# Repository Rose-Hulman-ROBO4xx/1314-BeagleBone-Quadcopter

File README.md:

Snoopy Copter
==========================
The quadcopter project got a rename recently. Named for the popular Peanuts character Snoopy, who always dreamed of flight, our flying Beaglebone will hopefully aid Snoopy in his quest to defeat the Red Baron!

Create an inexpensive open-source project for a BeagleBone cape quadcopter. As of the beginning of April, 2014, we have flight! Some videos of the initial flight testing are located [here](https://www.dropbox.com/sh/0pfk43b3zq14rjh/xk6Kl6lccb#/). Since then, the quadcopter has gotten easier to fly and more stable.

## Pictures ##

421 grams!

## License ##
All software and hardware designs (frame, circuit board, etc.) here are under Creative Commons Non-Commercial Share-Alike V3.0 License, located [here](http://creativecommons.org/licenses/by-nc-sa/3.0/us/legalcode).

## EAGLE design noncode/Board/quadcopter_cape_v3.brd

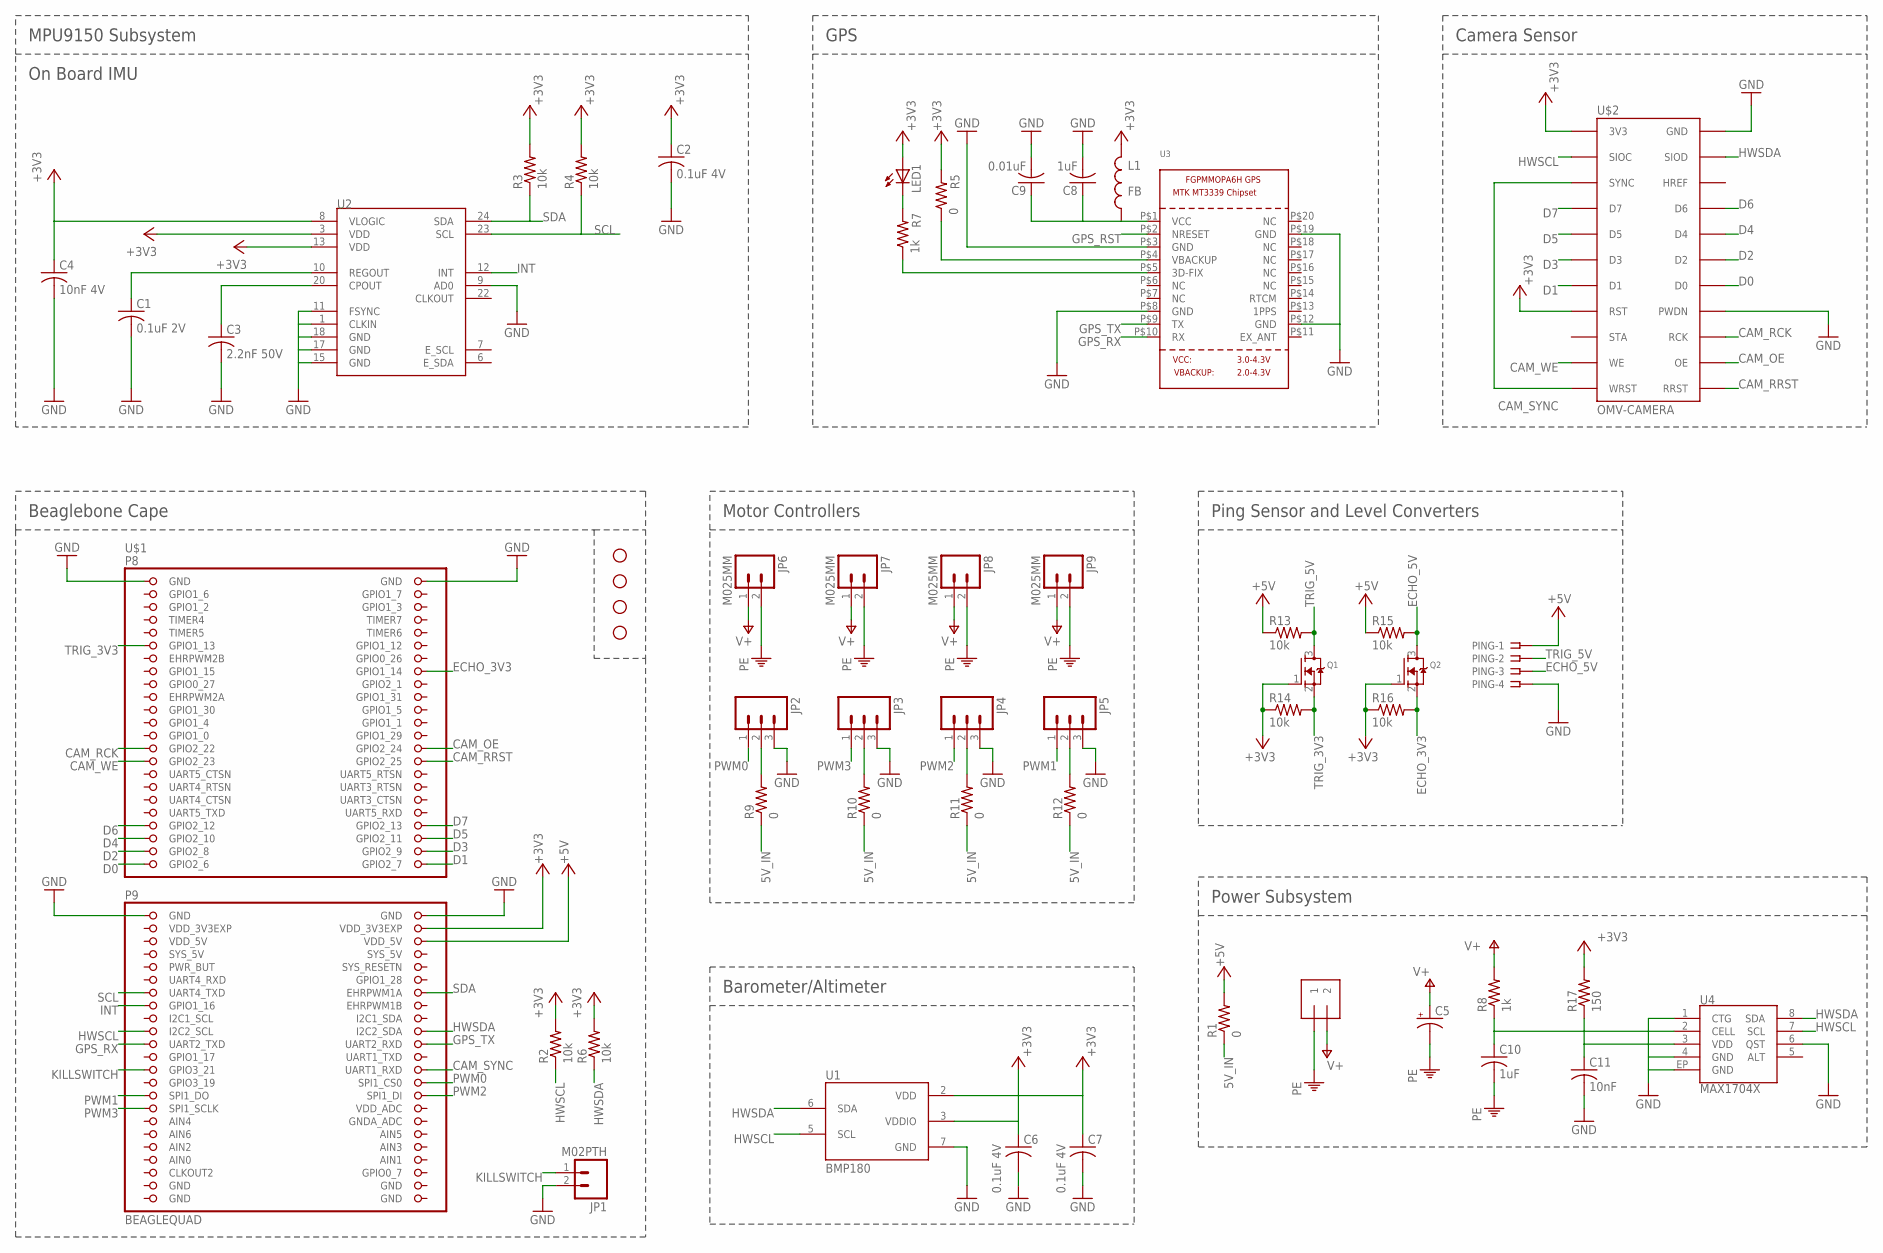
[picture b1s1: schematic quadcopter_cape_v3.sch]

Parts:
C1: 0.1uF 2V; C0805
C2, C6, C7: 0.1uF 4V; C0805
C3: 2.2nF 50V; C0805
C4: 10nF 4V; C0805
C5: 10UF-25V-20%(PTH); CPOL-RADIAL-10UF-25V
C8, C10: 1uF; C0805
C9: 0.01uF; C0805
C11: 10nF; C0805
JP1: M02PTH; 1X02
JP2, JP3, JP4, JP5: M03PTH; 1X03
JP6, JP7, JP8, JP9: M025MM; SCREWTERMINAL-5MM-2
L1: FB; 0805
LED1: LEDCHIP-LED0805; CHIP-LED0805
PING: SSW-104-02-S-S-RA
Q1, Q2: MOSFET-NREFLOW; SOT23
R1, R5, R9, R10, R11, R12: 0; M0805
R2, R3, R4, R6, R13, R14, R15, R16: 10k; M0805
R7, R8: 1k; M0805
R17: 150; M0805
STANDOFF1, STANDOFF2, STANDOFF3, STANDOFF4: STAND-OFF
U1: BMP180
U2: MPU-9150QFN-24-NP; QFN-24-NP
U3: GPS_FGPMMOPA6H; FGPMMOPA6H
U4: MAX1704X; TDFN-8
U$1: BEAGLEQUAD; BEAGLEQUAD_SHIELD
U$2: OMV-CAMERA
U$3: 1X2-12AWG

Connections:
5V_IN: R1.1, R9.1, R10.1, R11.1, R12.1
+3V3: C2.1, C4.1, C6.1, C7.1, L1.2, LED1.A, Q1.1 (G), Q2.1 (G), R2.2, R3.2, R4.2, R5.2, R6.2, R14.1, R16.1, R17.2, U1.2 (VDD), U1.3 (VDDIO), U2.3 (VDD), U2.8 (VLOGIC), U2.13 (VDD), U$1.50 (VDD_3V3EXP), U$2.3V3, U$2.RST
+5V: PING.1, R1.2, R13.1, R15.1, U$1.52 (VDD_5V)
AIN0: U$1.85 (AIN0)
CAM_OE: U$1.28 (GPIO2_24), U$2.OE
CAM_RCK: U$1.27 (GPIO2_22), U$2.RCK
CAM_RRST: U$1.30 (GPIO2_25), U$2.RRST
CAM_SYNC: U$1.72 (UART1_RXD), U$2.SYNC, U$2.WRST
CAM_WE: U$1.29 (GPIO2_23), U$2.WE
D0: U$1.45 (GPIO2_6), U$2.D0
D1: U$1.46 (GPIO2_7), U$2.D1
D2: U$1.43 (GPIO2_8), U$2.D2
D3: U$1.44 (GPIO2_9), U$2.D3
D4: U$1.41 (GPIO2_10), U$2.D4
D5: U$1.42 (GPIO2_11), U$2.D5
D6: U$1.39 (GPIO2_12), U$2.D6
D7: U$1.40 (GPIO2_13), U$2.D7
ECHO_3V3: Q2.2 (S), R16.2, U$1.16 (GPIO1_14)
ECHO_5V: PING.3, Q2.3 (D), R15.2
GND: C1.2, C2.2, C3.2, C4.2, C6.2, C7.2, C8.2, C9.2, C11.2, JP1.2, JP2.3, JP3.3, JP4.3, JP5.3, PING.4, U1.7 (GND), U2.1 (CLKIN), U2.9 (AD0), U2.11 (FSYNC), U2.15 (GND), U2.17 (GND), U2.18 (GND), U3.P$3 (GND), U3.P$8 (GND), U3.P$12 (GND), U3.P$19 (GND), U4.1 (CTG), U4.4 (GND), U4.6 (QST), U4.EP (GND), U$1.1 (GND), U$1.2 (GND), U$1.47 (GND), U$1.48 (GND), U$1.89 (GND), U$1.90 (GND), U$1.91 (GND), U$1.92 (GND), U$2.GND, U$2.PWDN
GPS_RST: U3.P$2 (NRESET)
GPS_RX: U3.P$10 (RX), U$1.67 (UART2_TXD)
GPS_TX: U3.P$9 (TX), U$1.68 (UART2_RXD)
HWSCL: R2.1, U1.5 (SCL), U4.7 (SCL), U$1.65 (I2C2_SCL), U$2.SIOC
HWSDA: R6.1, U1.6 (SDA), U4.8 (SDA), U$1.66 (I2C2_SDA), U$2.SIOD
INT: U2.12 (INT), U$1.61 (GPIO1_16)
KILLSWITCH: JP1.1, U$1.71 (GPIO3_21)
unnamed: C10.1, R8.1, U4.2 (CELL)
unnamed: C1.1, U2.10 (REGOUT)
unnamed: R5.1, U3.P$4 (VBACKUP)
unnamed: C3.1, U2.20 (CPOUT)
unnamed: R7.1, U3.P$5 (3D-FIX)
unnamed: LED1.C, R7.2
unnamed: C8.1, C9.1, L1.1, U3.P$1 (VCC)
unnamed: JP2.2, R9.2
unnamed: JP3.2, R10.2
unnamed: JP4.2, R11.2
unnamed: JP5.2, R12.2
unnamed: C11.1, R17.1, U4.3 (VDD)
PE: C5.2 (-), C10.2, JP6.2, JP7.2, JP8.2, JP9.2, U$3.P$1 (1)
PWM0: JP2.1, U$1.74 (SPI1_CS0)
PWM1: JP5.1, U$1.75 (SPI1_DO)
PWM2: JP4.1, U$1.76 (SPI1_DI)
PWM3: JP3.1, U$1.77 (SPI1_SCLK)
SCL: R4.1, U2.23 (SCL), U$1.59 (UART4_TXD)
SDA: R3.1, U2.24 (SDA), U$1.60 (EHRPWM1A)
SYS_5V: U$1.53 (SYS_5V)
TRIG_3V3: Q1.2 (S), R14.2, U$1.11 (GPIO1_13)
TRIG_5V: PING.2, Q1.3 (D), R13.2
V+: C5.1 (+), JP6.1, JP7.1, JP8.1, JP9.1, R8.2, U$3.P$2 (2)
VDD_3V3EXP: U$1.49 (VDD_3V3EXP)
VDD_5V: U$1.51 (VDD_5V)

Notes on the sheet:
Beaglebone Cape
Motor Controllers
MPU9150 Subsystem
On Board IMU
Power Subsystem
Ping Sensor and Level Converters
Camera Sensor
Barometer/Altimeter
GPS

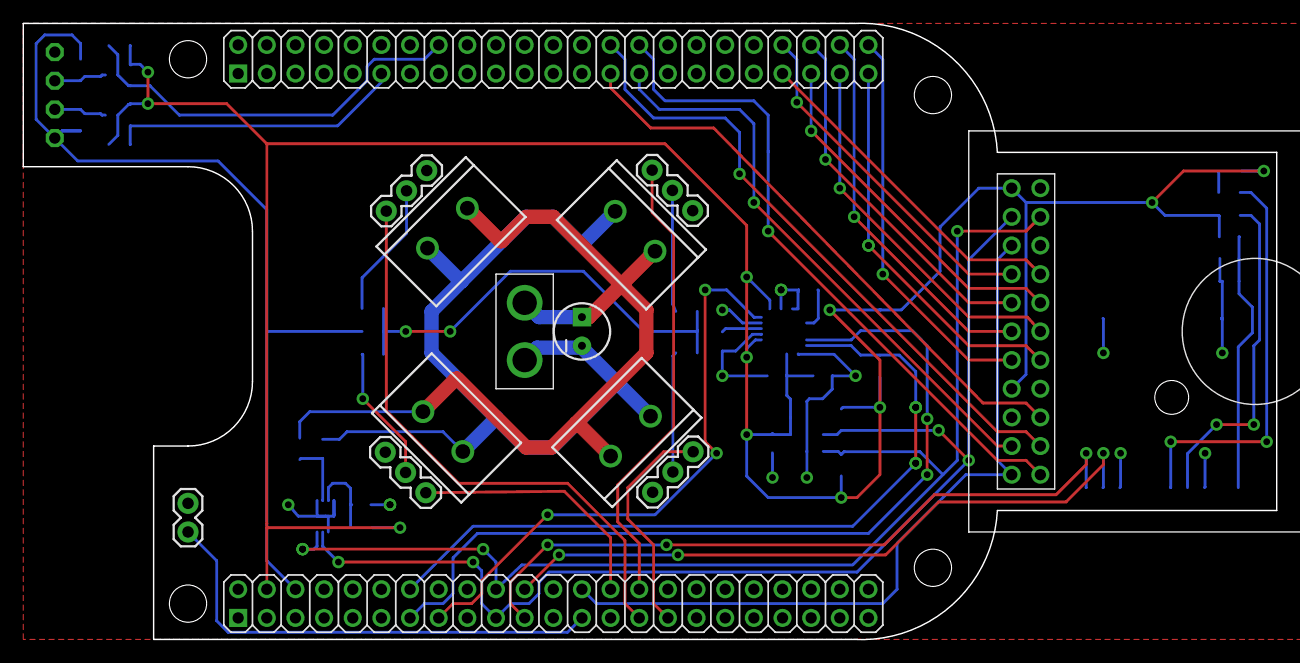
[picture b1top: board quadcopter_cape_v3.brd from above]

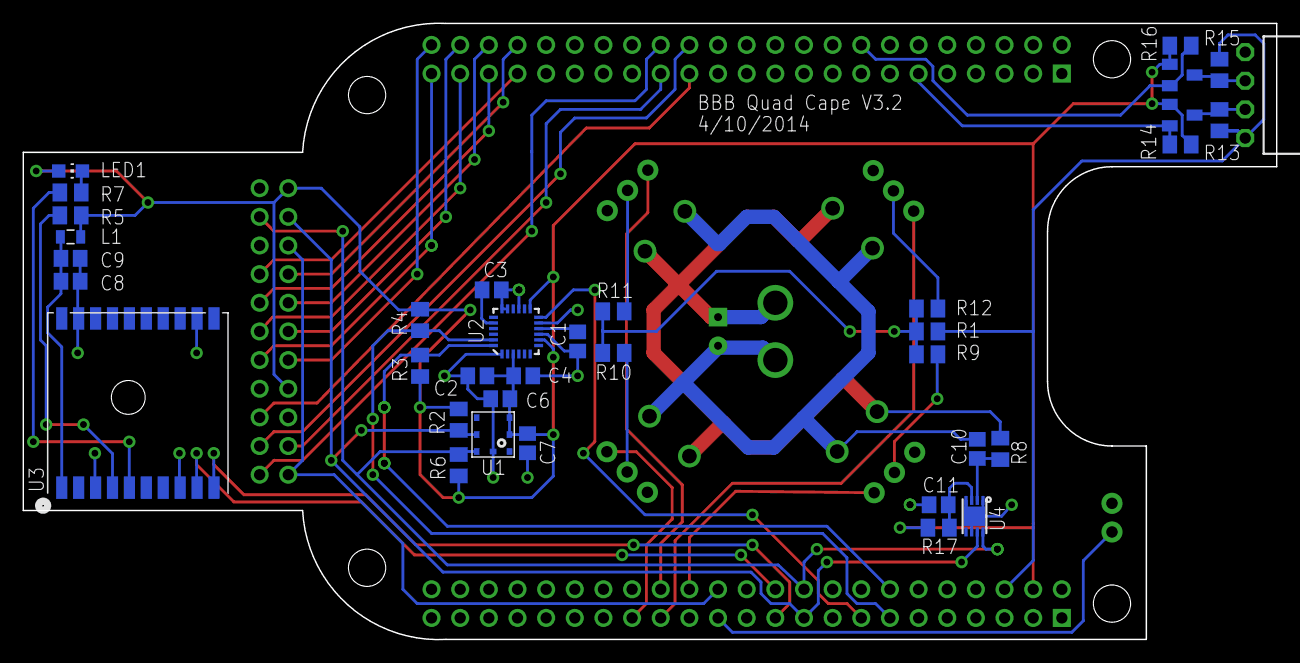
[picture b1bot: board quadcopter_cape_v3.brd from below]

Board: 2 copper layers, 111.1 x 54.6 mm, 53 parts (36 on the bottom side), 47 nets.

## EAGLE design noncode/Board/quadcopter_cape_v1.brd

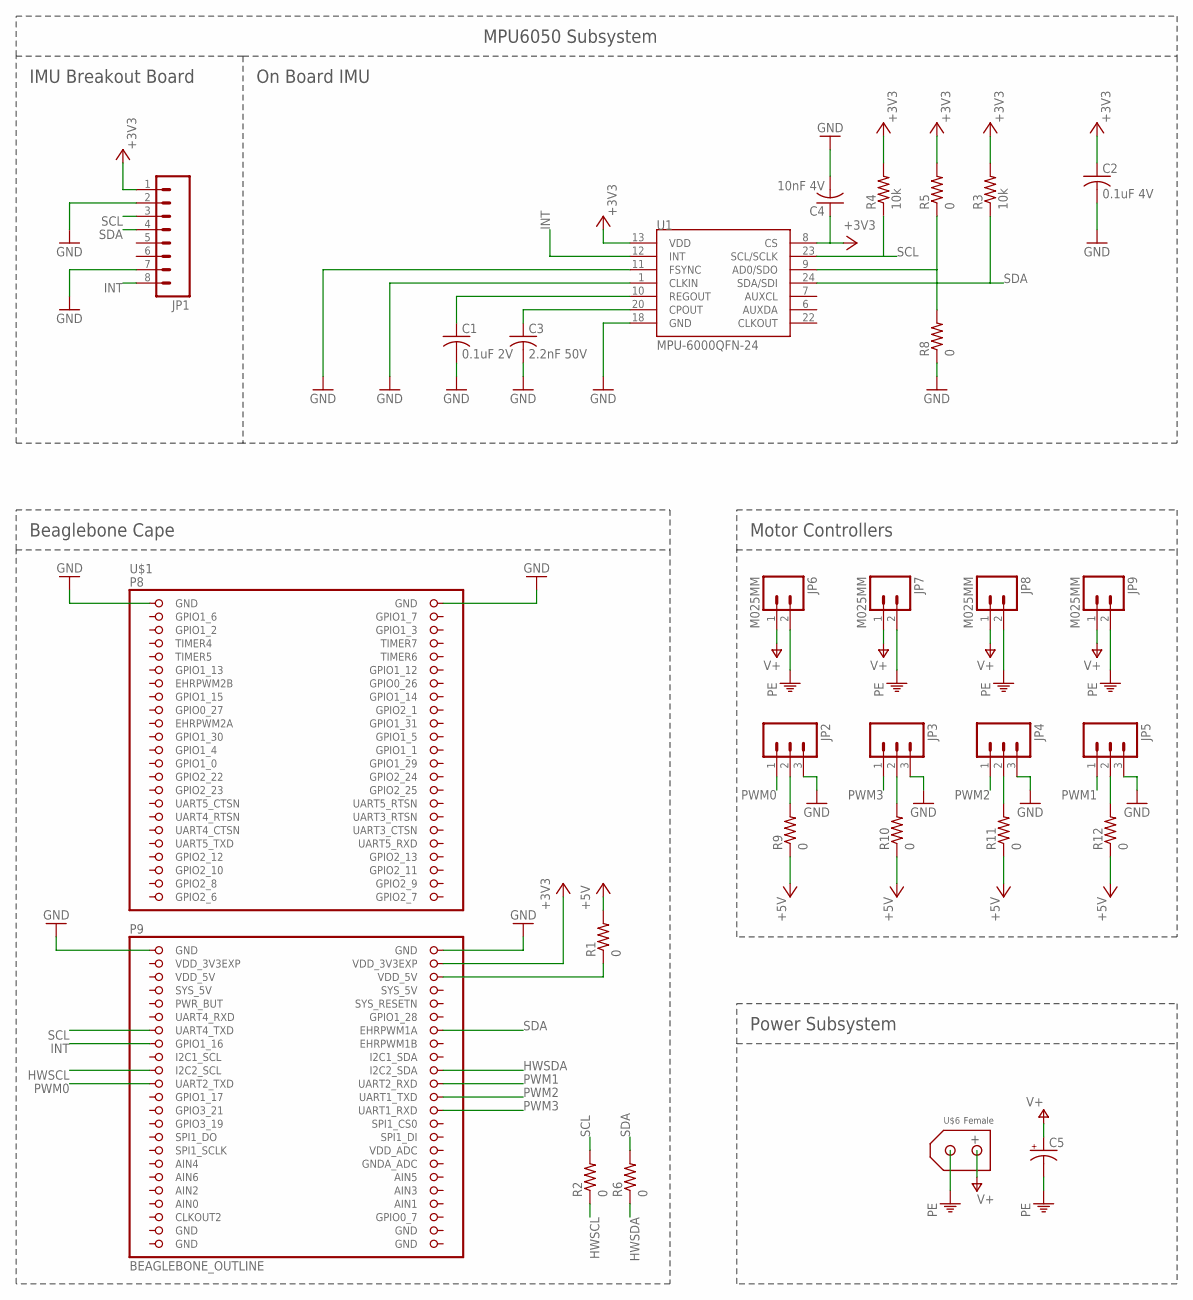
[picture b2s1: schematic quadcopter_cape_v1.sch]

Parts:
C1: 0.1uF 2V; C0603
C2: 0.1uF 4V; C0603
C3: 2.2nF 50V; C0603
C4: 10nF 4V; C0603
C5: 10UF-25V-20%(PTH); CPOL-RADIAL-10UF-25V
JP1: M081X08; 1X08
JP2, JP3, JP4, JP5: M03PTH; 1X03
JP6, JP7, JP8, JP9: M025MM; SCREWTERMINAL-5MM-2
R1, R2, R5, R6, R8, R9, R10, R11, R12: 0; R0603
R3, R4: 10k; R0603
U1: MPU-6000QFN-24; QFN-24-TESTING
U$1: BEAGLEBONE_OUTLINE; BEAGLEBONE_SHIELD
U$6: XT60

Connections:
+3V3: C2.1, C4.1, JP1.1, R3.2, R4.2, R5.2, U1.8 (CS), U1.13 (VDD), U$1.50 (VDD_3V3EXP)
+5V: R1.2, R9.1, R10.1, R11.1, R12.1
AIN0: U$1.85 (AIN0)
GND: C1.2, C2.2, C3.2, C4.2, JP1.2, JP1.7, JP2.3, JP3.3, JP4.3, JP5.3, R8.1, U1.1 (CLKIN), U1.11 (FSYNC), U1.18 (GND), U$1.1 (GND), U$1.2 (GND), U$1.47 (GND), U$1.48 (GND), U$1.89 (GND), U$1.90 (GND), U$1.91 (GND), U$1.92 (GND)
HWSCL: R2.1, U$1.65 (I2C2_SCL)
HWSDA: R6.1, U$1.66 (I2C2_SDA)
INT: JP1.8, U1.12 (INT), U$1.61 (GPIO1_16)
unnamed: R1.1, U$1.52 (VDD_5V)
unnamed: C1.1, U1.10 (REGOUT)
unnamed: C3.1, U1.20 (CPOUT)
unnamed: R5.1, R8.2, U1.9 (AD0/SDO)
unnamed: JP2.2, R9.2
unnamed: JP3.2, R10.2
unnamed: JP4.2, R11.2
unnamed: JP5.2, R12.2
PE: C5.2 (-), JP6.2, JP7.2, JP8.2, JP9.2, U$6.GND
PWM0: JP2.1, U$1.67 (UART2_TXD)
PWM1: JP5.1, U$1.68 (UART2_RXD)
PWM2: JP4.1, U$1.70 (UART1_TXD)
PWM3: JP3.1, U$1.72 (UART1_RXD)
SCL: JP1.3, R2.2, R4.1, U1.23 (SCL/SCLK), U$1.59 (UART4_TXD)
SDA: JP1.4, R3.1, R6.2, U1.24 (SDA/SDI), U$1.60 (EHRPWM1A)
SYS_5V: U$1.53 (SYS_5V)
V+: C5.1 (+), JP6.1, JP7.1, JP8.1, JP9.1, U$6.PWR
VDD_3V3EXP: U$1.49 (VDD_3V3EXP)
VDD_5V: U$1.51 (VDD_5V)

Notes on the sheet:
Beaglebone Cape
Motor Controllers
IMU Breakout Board
MPU6050 Subsystem
On Board IMU
Power Subsystem
Female

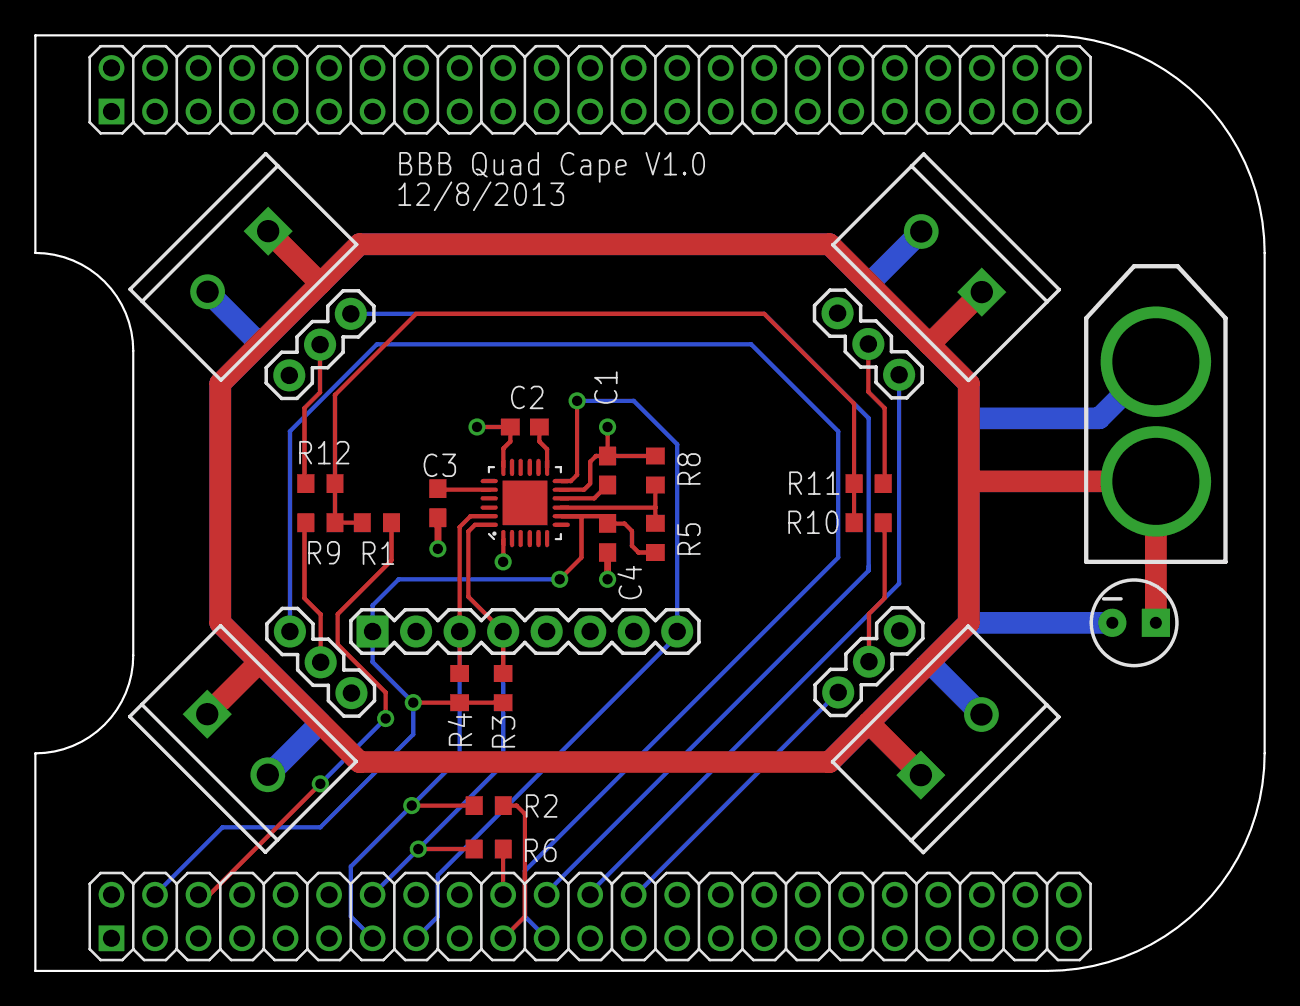
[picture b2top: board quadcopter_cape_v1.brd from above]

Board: 2 copper layers, 71.8 x 54.6 mm, 28 parts (0 on the bottom side), 22 nets.

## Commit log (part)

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2000-01-01 Committing current beagle status
2000-01-01 camera
2000-01-01 commiting pwm stuff before branching to 2-wire imu
2000-01-01 committing before sharing code for problemsolving on irc
2000-01-01 added basic script for controller
2000-01-01 ping not working
2000-01-01 Changed parsing method
2000-01-01 added comments for what header pin each control line is connected to in the pru i2c bitbanging code
2000-01-01 added rev1 and rev2 overlays
2000-01-01 now the address argument to the i2c functions is the actual address, not it shifted left.
2000-01-01 fifo
2000-01-01 Modified readme
2000-01-01 organized files and working on joystick with FIFO
2000-01-01 Trying to add last two channels to pwm
2000-01-01 stuf
2000-01-01 got camera working, the endianess was backwards
2000-01-01 organized file structure and committed changes
2000-01-01 commented out ping code, made it quicker to change between rev1 and rev 2 in pwm code, added back safties
2000-01-01 fixed analogous values to the standard 32680
2000-01-01 Added user parameter setting, land function, hover function, fixed data sending
2000-01-01 simple complementary filter working
2000-01-01 Fixed contorl data spamming
2000-01-01 Working on joystick
2000-01-01 commiting before trying an older branch
2000-01-01 fixed return register define statement
2000-01-01 resets PID loops and kills motors if throttle is off
2000-01-01 added streaming image update function
2000-01-01 fixed control data bug
2000-01-01 changed the image file directory
2000-01-01 got the control algorithm calibration function working
2000-01-01 minor fix
2000-01-01 the fix I did before wasn't necessary
2000-01-01 got pwm working
2000-01-01 Better event algorithm and standard values
2000-01-01 PID pitch and roll have fast response times with little overshoot and oscillations
2000-01-01 refactored to separate constants, structs, and function prototypes; also, this is a pretty good version of the demo as it is stable, generally around the right angle
2000-01-01 Single time calibration for IMU (file) and pin resolution
2000-01-01 new control call method, improved css, control data stringified to standard, analog values standardized, data spamming reduction code, overall code cleaning
2000-01-01 made a simple interface for ARM side programs to talk to the PRU
2000-01-01 commiting before handing over to ryan
2000-01-01 imu data might be a little broken
2000-01-01 Added joystick control and read/write to FIFO is working again (IDK what happened to it again, but it is fixed now)
2000-01-01 added tmp101 onto the bus, removed debug messages
2013-09-12 Adding TODO to prove that I can push changes to the repo. Others should do this as well.
2013-09-12 Fixed [ ] for markdown lists (must add space).
2013-09-12 Update README.md
    Markdown task lists don't seem to work...
2013-09-23 Adding the .tex file for the project proposal (and build byproducts) along with the directory to the repo.
2013-09-24 Updated the .tex file to include email addresses, a change log, the exec summary, and the walkthrough.
2013-09-25 Updated the Project Proposal with the diagrams.
2013-10-18 arduino i2c bit bang
2013-10-21 Adding pru stuff, the i2c example is in the example_apps/PRU_memQAccessPRUDataRam folder
2013-10-22 PRU I2C is working
2013-10-22 cleanup of the pru i2c
2013-10-23 more cleanup
2013-10-23 adding base device tree. It disables the heartbeat LED, and more importantly, enables the PRU hardware. Back up the original in /boot, and copy this one there.
2013-10-29 more cleanup, this time making the file names less cumbersome
2013-11-02 this should help stop the pru from being stupid, and start responding
2013-11-02 something to test the pru quickly
2013-11-02 trying changing the pwm loop to see if that's the problem
2013-11-03 test pru stuff
2013-11-03 really just committing the pwm stuff and the blink example
2013-11-05 script to setup the pru
2013-11-06 two wire is almost working, committing as a milestone type thing
2013-11-06 2 channel pwm is working, still a timing issue to work out before moving on to 3 and 4 channels
2013-11-06 I resolved the timing issue! moving to X channels should be trivial now.
2013-11-06 two wire imu working
2013-11-06 still working on things
2013-11-10 IMU TWO WIRE IS WORKING
2013-11-10 changed the sample rate, uncommeted some other stuff
2013-11-13 Fixed saftey issue where pwm would go to half throttle at start. removed unecessary imu.c code, made imu.c print to stdout and out.csv, changed imu gpio ports for proof that it's easy reconfigured in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
2013-12-04 initial connecting of modules
2013-12-04 included files instead of dumping them all in one monolithic source file
2013-12-04 modified imu.p to have a get_data function
2013-12-08 ControlAlgorithm c code added - there are TODO's in the code with things that need to be changed, expanded, or added
2013-12-10 Moved things to the proper repo (from my personal one to the team quadcopter repo).
2013-12-10 Updated the readme, changed the name of the service and the path required.
2013-12-10 Added all the files for the beagle quad server. There will probably be more...
2013-12-10 Added in css file
2013-12-10 Added a test button to demonstrate socket.io callbacks (how neat was that?)
2013-12-10 removing Overview.txt
2013-12-11 adding joystick example
2013-12-11 add a comment telling how to install joystick
2013-12-14 Updated some initializations for motor control
2013-12-15 Added a few comments about the code and some possibly suggestions. (everything has (Mike) after it, so just search for that).
2013-12-16 Added key bindings for LRUD and WASD for quadcopter control. Possibly didn't actually commit the changes in the control algorithm I claimed to commit earlier.
2013-12-16 fixed some gyro problems. Pitch still isn't working right for whatever reason.
2013-12-18 asdf
2013-12-18 added signal handler for ctrl+c to quit cleanly
2013-12-18 fixed axis system thing
2013-12-18 working on pwm
2013-12-18 committing pwm before making a new attempt at it
2013-12-18 adding more files for new pwm
2013-12-18 got pwm working again
2013-12-18 merged working pwm into control_alg
2013-12-18 Control Server Tower | added home page html css and js
2013-12-20 committing before break. Start of control algorithm, pwm is working.
2014-01-08 Adding an author file
2014-01-08 Added my user file to authors.
2014-01-08 added an author file
2014-01-08 Added an author file.
2014-01-08 Added member
2014-01-08 Committing the All Authors file (Make sure to pull before adding, and deal with conflits as they appear).
2014-01-08 Class activity file.
2014-01-08 added my name
2014-01-08 Added my name.
2014-01-08 Moved some files around into the code and non-code folders.
2014-01-08 Update AllAuthors.txt
    Added my name to authors
2014-01-08 Added author
2014-01-08 Initial layout with header completed
2014-01-12 Added pictures of the quadcopter as of the 12/18 meeting.
2014-01-12 things
2014-01-13 final commit before moving to new server...
2014-01-13 new code from old repo
2014-01-21 demo ready for rockwell
2014-01-22 camera code
2014-01-24 debian
2014-01-25 chnaged order of gpio in dto
2014-01-25 herp
2014-01-25 added kill switch
2014-01-26 updated setup script to build device tree overlay, load the overlay, and start the camera clock.
2014-01-29 added pin allocations for next board rev
2014-02-02 documented some of the constraints
2014-02-02 Changed gyro and accelerometer sensitivity settings to +/- 2g and +/- 250 deg/s.
2014-02-05 added saftey to pwm, cleaned up pwm, fixed memory bugs in control_alg
2014-02-09 The inital commit of the new website with updated CSS, HTML, and read to FIFO functionality
2014-02-09 added Website
2014-02-17 changes to the website javascript, improvements to flight
2014-02-17 xbox working
2014-02-17 stable flight and such
2014-02-17 xenomai
2014-02-17 changed message format
2014-02-17 changed pid, fixed makefile
2014-02-17 REALLY fixed the makefile.
2014-02-19 Added joystick code
2014-03-16 committing before switching branch (chris)
2014-03-16 ping sensor working
2014-03-16 working ultrasound and pwm
2014-03-18 working color
2014-03-18 working video recording
2014-03-26 moving to rev2 hopefully for good. pwm is borken in this rev
2014-03-29 fixed pru direct io and return address register issue in pru
2014-03-29 pid working properly yay
2014-03-30 here you go ryan.
2014-04-02 updated pin allocations
2014-04-02 updated pins
2014-04-05 this code is technically capable of flight, albeit very unstable flight.
2014-04-07 made python script for calibrating pid values
2014-04-07 added more features to the calibrate code
2014-04-07 updated bluetooth connection to create a bluetooth link between a host and the bone and share the internet connection
2014-04-07 updated ultrasound pins
2014-04-07 added pid stuff
2014-04-07 added new safety so if the program crashes the pru will quit within a second
2014-04-08 Added CAD files
2014-04-08 fixed a ui yaw problem, added a safety where it won't throttle up unless it sees a zero throttle first.
2014-04-08 Organized CAD files
2014-04-10 Update README.md
    Added license (CC-BY-SA) V3.0
2014-04-10 Update README.md
    Changed it to be more friendly (eliminate cruft). Next step... refactor file structure!
2014-04-10 Update README.md
    Added current branch note.
2014-04-10 Update README.md
    Updated to reflect other branch. Probably should have just pulled over...
2014-04-11 Adding parts for an assembled quadcopter
2014-04-11 Added tabs to parts to keep them on one sheet
2014-04-13 ABANDON BONE.
2014-04-13 scripts for starting bone
2014-04-14 Adding new images of the BeagleQuad
2014-04-14 Update README.md
    Added pictures of the quadcopter to the readme
2014-04-16 Update README.md
    Changed CC-BY-SA to CC-BY-NC-SA.
2014-04-16 Update README.md
    Bumped license to Non-Commercial.
2014-04-17 Update README.md
    Renamed the project.
2014-04-23 cleanup
2014-04-23 camera now saves bmps, changed shebang line for server, moved pid_values.txt, cleanup
2014-05-05 Added V1-3.2 schematics and board layout files, as well as the most up to date bill of materials
2014-05-10 cleaning
2014-05-10 don't have prebuilt binaries
2014-05-11 Adding pictures of the board
2014-05-11 Added 3.2 board
2014-05-11 more scripts
2014-05-11 Adding PID pictures
2014-05-16 create tmpfs in setup_pru.sh, change camera program
2014-05-26 done
2014-09-28 Update README.md
    Uploaded videos to youtube and removing them from dropbox.
2016-04-21 Update README.md
    added a subtitle to the last picture to point out the units of the scale.
2016-04-21 testing that I can still commit
2017-06-07 Created a script that knows how to read from the serial receiver.
2017-06-07 add example script that knows how to read serial receiver
2017-06-07 Remove lines from readme that are no longer true.
2019-01-20 fixed unhandled merge conflict

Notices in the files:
parts and their libraries:
SparkFun-Sensors: Licensing: CC v3.0 Share-Alike You are welcome to use this library for commercial purposes.
